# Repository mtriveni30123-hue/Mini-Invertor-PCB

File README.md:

# Mini Inverter PCB Design

## Tools
- KiCad

## Features
- Complete schematic
- PCB layout
- 3D PCB model

## Learning Outcome
- Schematic to PCB workflow
- Component placement & routing

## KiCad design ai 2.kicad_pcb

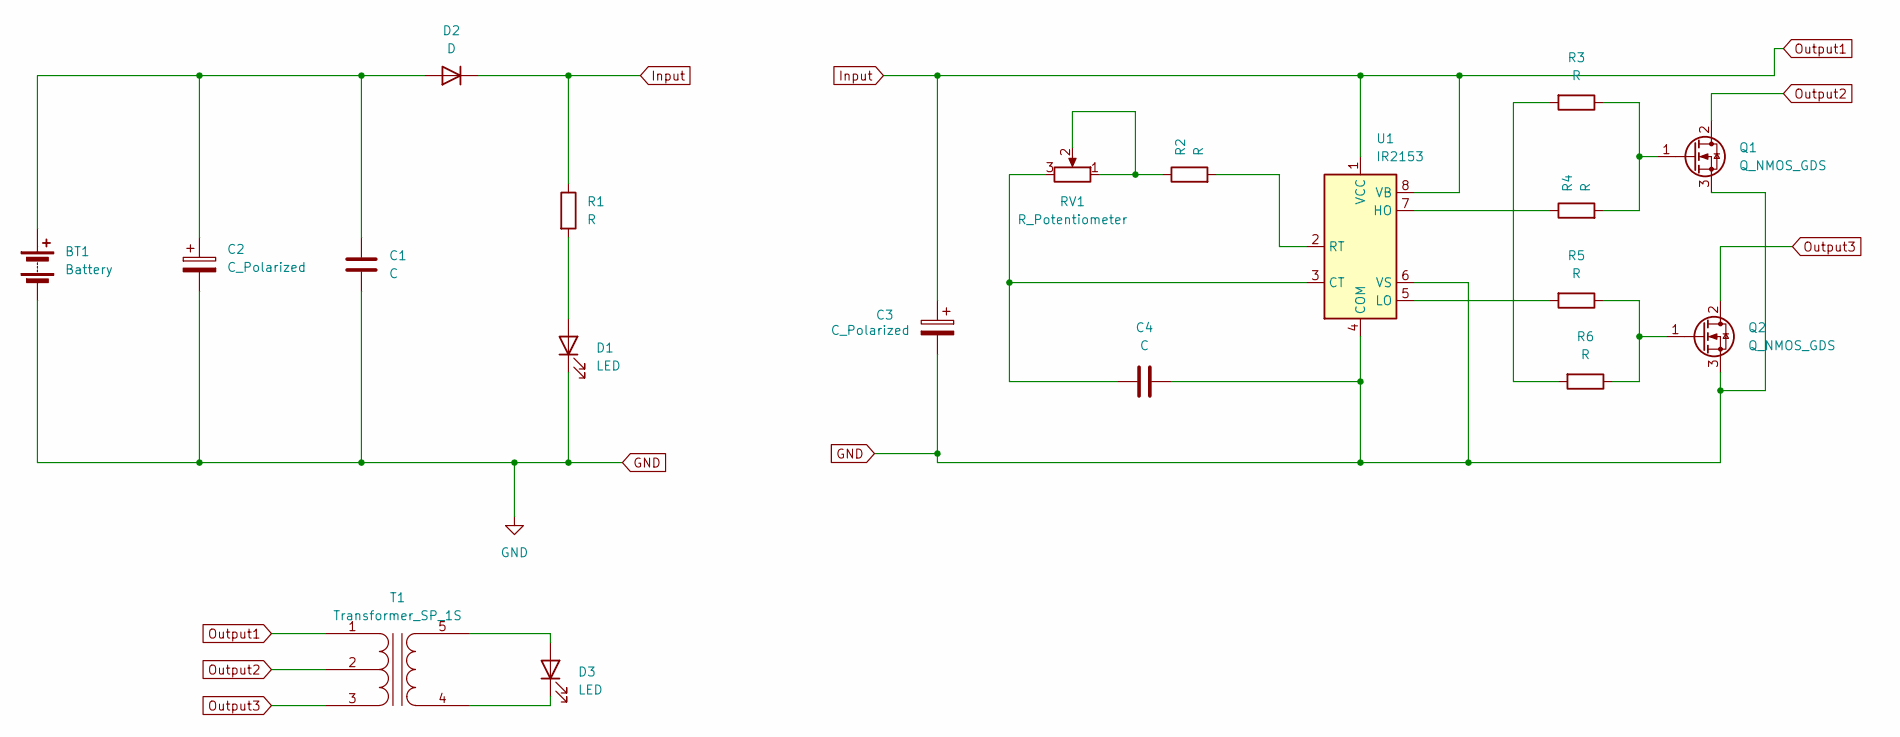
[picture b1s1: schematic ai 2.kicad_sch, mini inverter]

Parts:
BT1: Battery; CP_Radial_D8.0mm_P3.50mm
C1: C; CP_Radial_D8.0mm_P3.50mm
C2, C3: C_Polarized; C_Disc_D5.0mm_W2.5mm_P5.00mm
C4: C; C_Disc_D5.0mm_W2.5mm_P5.00mm
D1, D3: LED; LED_D5.0mm
D2: D; D_DO-41_SOD81_P7.62mm_Horizontal
Q1, Q2: Q_NMOS_GDS; TO-220-3_Vertical
R1, R2, R3, R4, R5, R6: R; R_Axial_DIN0207_L6.3mm_D2.5mm_P7.62mm_Horizontal
RV1: R_Potentiometer; Potentiometer_Bourns_3386W_Horizontal
T1: Transformer_SP_1S; TerminalBlock_Phoenix_MKDS-3-5-5.08_1x05_P5.08mm_Horizontal
U1: IR2153; DIP-8_W7.62mm

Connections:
GND: BT1.2 (-), C1.2, C2.2, C3.2, C4.2, D1.1 (K), Q1.3 (S), Q2.3 (S), U1.4 (COM), U1.6 (VS)
Input: C3.1, D2.1 (K), R1.1, T1.1 (PR1), U1.1 (VCC), U1.8 (VB)
unnamed: BT1.1 (+), C1.1, C2.1, D2.2 (A)
unnamed: D1.2 (A), R1.2
unnamed: D3.2 (A), T1.5 (S2)
unnamed: D3.1 (K), T1.4 (S1)
unnamed: Q1.1 (G), R3.1, R4.2
unnamed: Q2.1 (G), R5.1, R6.1
unnamed: R2.1, RV1.1, RV1.2
unnamed: R3.2, R6.2
unnamed: C4.1, RV1.3, U1.3 (CT)
unnamed: R4.1, U1.7 (HO)
unnamed: R5.2, U1.5 (LO)
unnamed: R2.2, U1.2 (RT)
Output2: Q1.2 (D), T1.2 (PM)
Output3: Q2.2 (D), T1.3 (PR2)

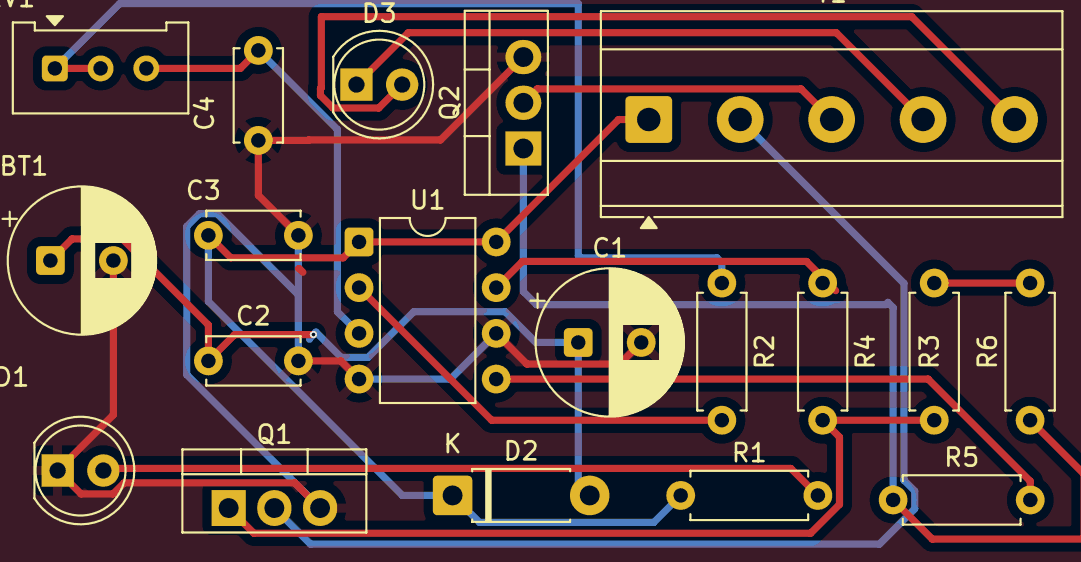
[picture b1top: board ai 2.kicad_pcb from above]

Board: 2 copper layers, 19 parts (0 on the bottom side), 16 nets.

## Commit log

2025-12-17 Revise README with project details and features
    Updated project title and added sections for tools, features, and learning outcomes.
